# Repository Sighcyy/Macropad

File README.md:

# KATOB Macropad
(Keyboard Are Too Big)
*Build Guide and Final Image will be added once completed

I designed a miniature gaming Macropad featuring 8 mechanical push-button switches, a rotary encoder, and an RGB LED for indication. It features an EC11 rotary encoder, 1 addressable RGB LED, and the Seeed XIAO RP2040 microcontroller, which was chosen for its small form factor and support for KMK firmware. The parts are populated on a custom PCB for tidy arrangement and good performance. The case is fully 3D printable, making the design easy to reproduce and customize. This Macropad provides a programmable, mini interface to enhance game control and responsiveness.

# Macropad PCB and Schematics Design

# Macropad CAD Design

Over the LED Light Hole, a thin layer of hard plastic will be added to allow light to pass through without the user being able to touch the inside. 

Reflection: *To be added

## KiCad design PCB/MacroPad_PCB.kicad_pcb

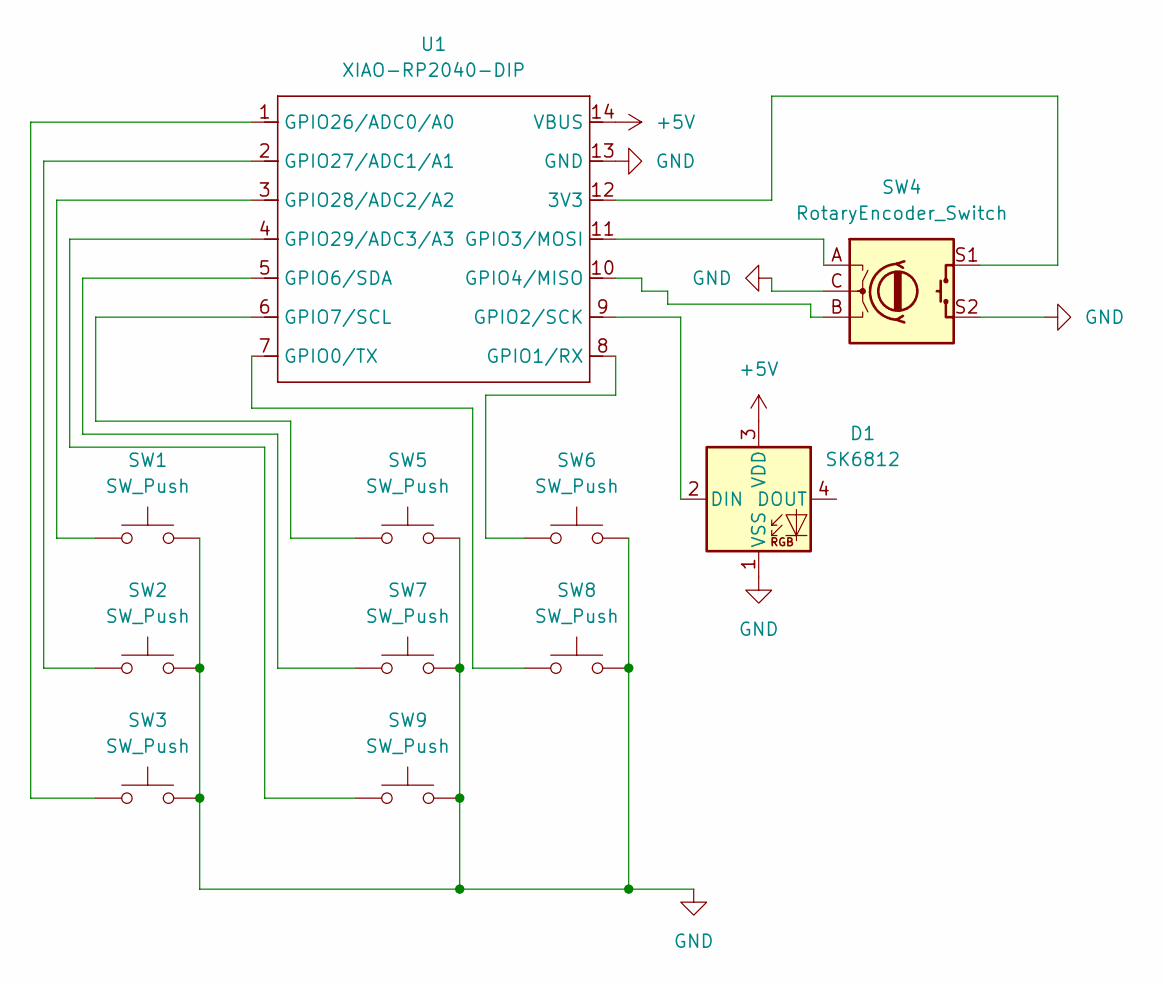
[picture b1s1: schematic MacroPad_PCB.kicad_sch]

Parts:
D1: SK6812; LED_SK6812_PLCC4_5.0x5.0mm_P3.2mm
SW1, SW2, SW3, SW5, SW6, SW7, SW8, SW9: SW_Push; SW_Cherry_MX_1.00u_PCB
SW4: RotaryEncoder_Switch; RotaryEncoder_Alps_EC11E-Switch_Vertical_H20mm
U1: XIAO-RP2040-DIP

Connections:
+5V: D1.3 (VDD), U1.14 (VBUS)
GND: D1.1 (VSS), SW1.2, SW2.2, SW3.2, SW4.C, SW4.S2, SW5.2, SW6.2, SW7.2, SW8.2, SW9.2, U1.13 (GND)
unnamed: D1.2 (DIN), U1.9 (GPIO2/SCK)
unnamed: SW4.S1, U1.12 (3V3)
unnamed: SW8.1, U1.7 (GPIO0/TX)
unnamed: SW6.1, U1.8 (GPIO1/RX)
unnamed: SW4.A, U1.11 (GPIO3/MOSI)
unnamed: SW4.B, U1.10 (GPIO4/MISO)
unnamed: SW7.1, U1.5 (GPIO6/SDA)
unnamed: SW5.1, U1.6 (GPIO7/SCL)
unnamed: SW3.1, U1.1 (GPIO26/ADC0/A0)
unnamed: SW2.1, U1.2 (GPIO27/ADC1/A1)
unnamed: SW1.1, U1.3 (GPIO28/ADC2/A2)
unnamed: SW9.1, U1.4 (GPIO29/ADC3/A3)

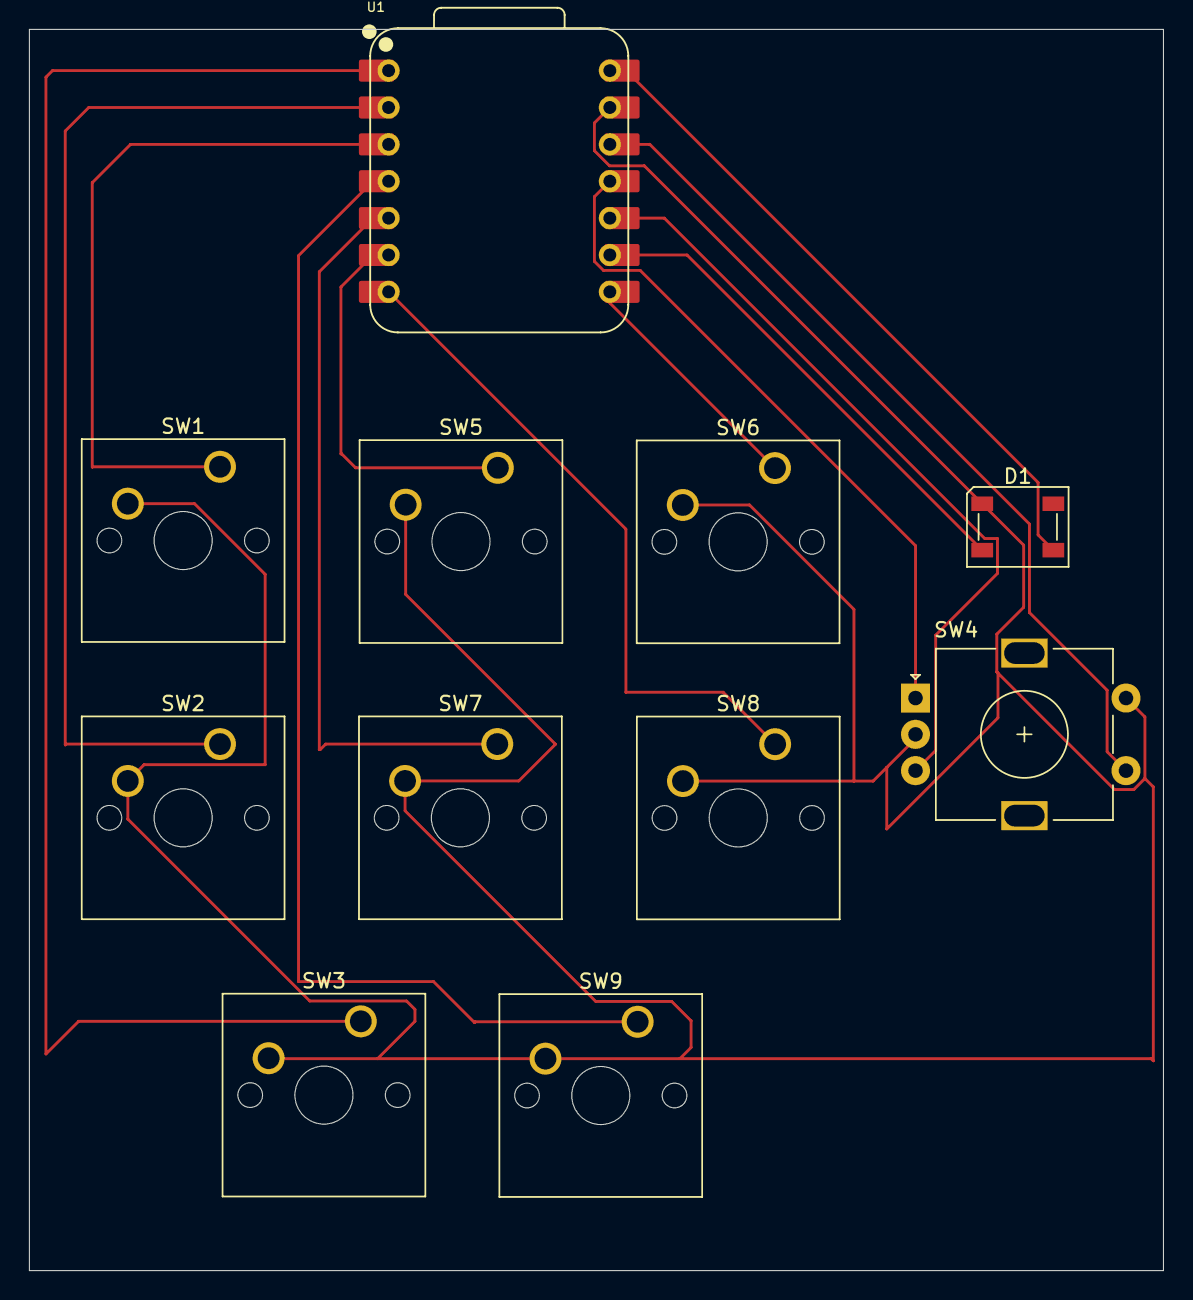
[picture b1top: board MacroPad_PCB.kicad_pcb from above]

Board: 2 copper layers, 78.1 x 85.5 mm, 11 parts (0 on the bottom side), 14 nets.

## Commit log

2025-06-16 Create smth
2025-06-16 Create Yes
2025-06-19 Create y
